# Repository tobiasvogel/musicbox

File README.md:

# MIDI Music Box

This is an improved version of the original musicbox project by [mitxela](https://github.com/mitxela/musicbox).

There are two major enhancements over the original version:
 - PCBs (Gerber and EAGLE) for the circuits as well as most of the mechanical parts
 - A (optional) addon-board featuring a Arduino MKR WiFi 1010 providing MIDI-file support from both microSD-cards and via WiFi (Webbrowser)

In the future I will furthermore add:
 * *BOM for all PCBs* (work-in-progress)
 * Renderings for visualization
 * Detailed assembly instructions

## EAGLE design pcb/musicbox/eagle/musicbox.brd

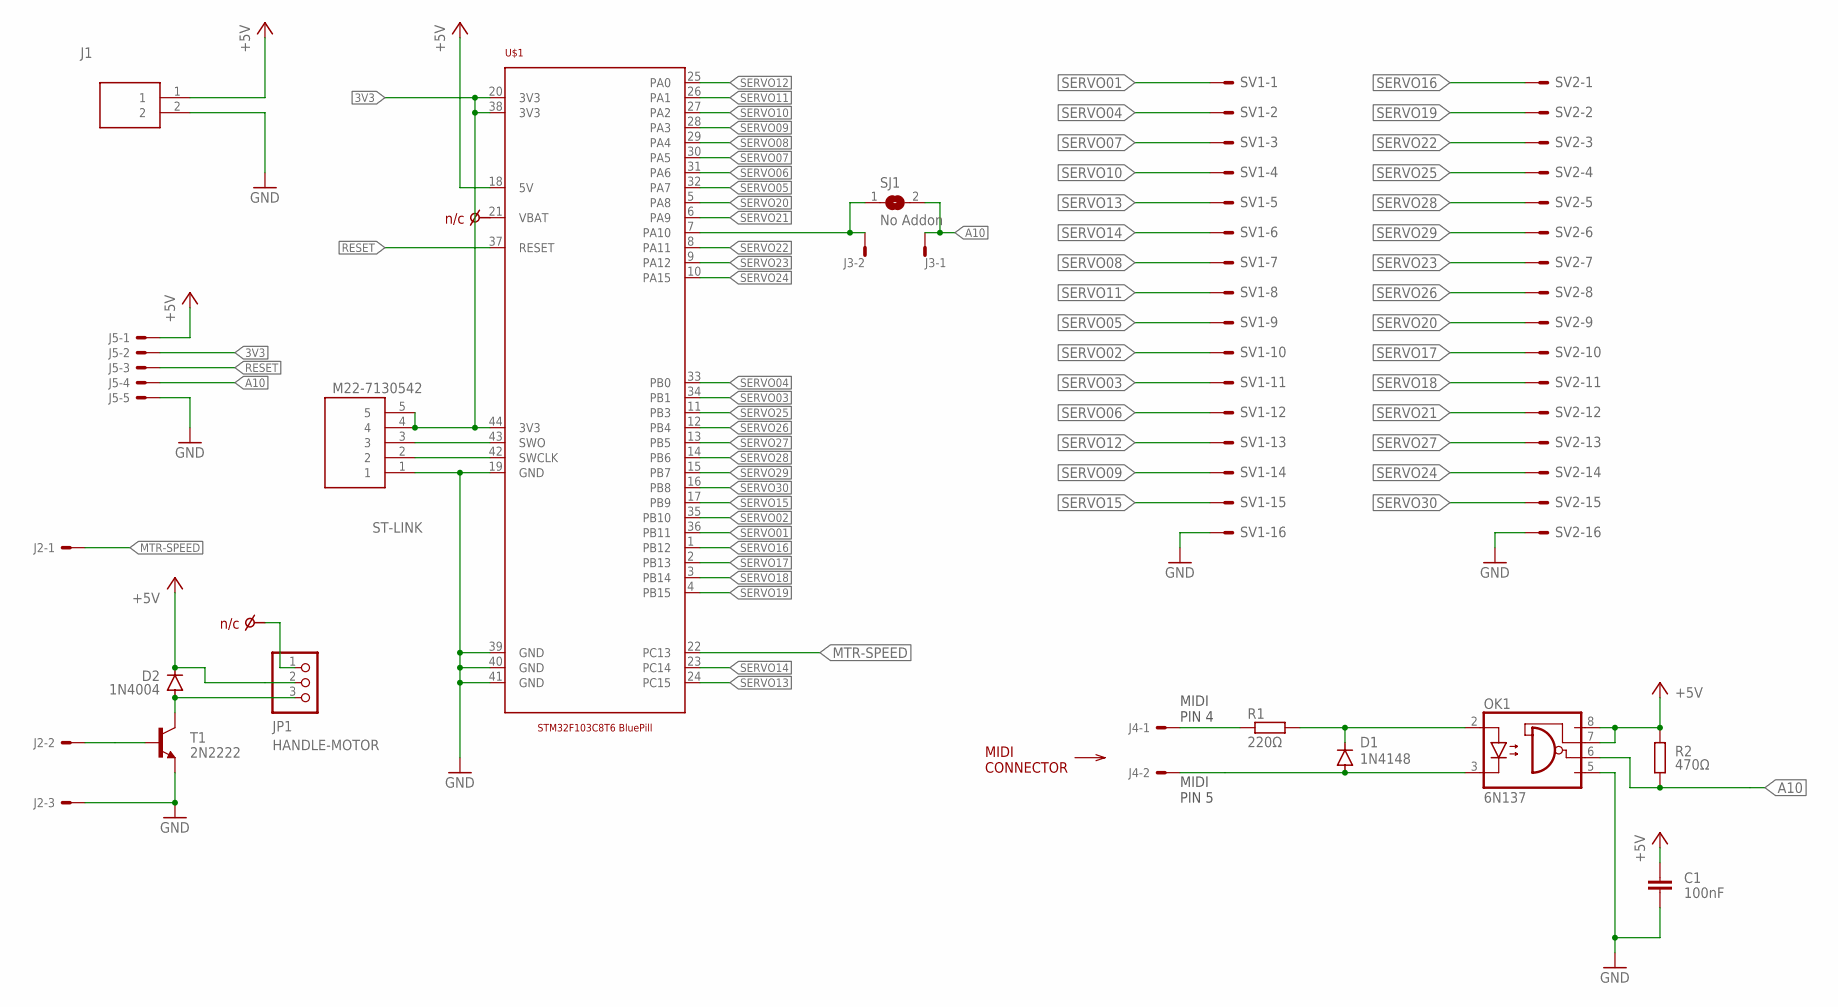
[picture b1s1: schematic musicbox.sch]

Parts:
C1: 100nF; C025-025X050; MOUSER_PART_NUMBER 594-K104M15X7RF53L2; DIGIKEY_PART_NUMBER BC5142-ND
D1: 1N4148; DO35-7; MOUSER_PART_NUMBER 512-1N4148; DIGIKEY_PART_NUMBER 1N4148FS-ND
D2: 1N4004; DO41-10; MOUSER_PART_NUMBER 583-1N4004-T; DIGIKEY_PART_NUMBER 1N4004MSCT-ND
J1: 1727010; DIGIKEY_PART_NUMBER 277-1947-ND
J2: 22-27-2031-03; 6410-03; MOUSER_PART_NUMBER 538-22-27-2031; DIGIKEY_PART_NUMBER WM4112-ND
J3, J4: 22-27-2021-02; 6410-02; MOUSER_PART_NUMBER 538-22-27-2021; DIGIKEY_PART_NUMBER WM4111-ND
J5: 22-27-2051-05; 6410-05; MOUSER_PART_NUMBER 538-22-27-2051; DIGIKEY_PART_NUMBER WM4114-ND
JP1: HANDLE-MOTOR; 1X03; MOUSER_PART_NUMBER 651-1012937890301BLF; DIGIKEY_PART_NUMBER 68004-403-ND
OK1: 6N137; DIL08; MOUSER_PART_NUMBER 859-6N137; DIGIKEY_PART_NUMBER 160-1791-ND
R1: 220Ω; 0207/7; MOUSER_PART_NUMBER 594-MBB02070C2200FCT; DIGIKEY_PART_NUMBER BC3666CT-ND
R2: 470Ω; 0207/7; MOUSER_PART_NUMBER 594-MBB02070C4700FCT; DIGIKEY_PART_NUMBER BC3790CT-ND
SJ1: No Addon; SJW
ST-LINK: M22-7130542; RHDR5W50P0X200_1X5_1050X240X44; DIGIKEY_PART_NUMBER 952-1352-5-ND
SV1: Servos 01-15; ML16; MOUSER_PART_NUMBER 617-09185166324; DIGIKEY_PART_NUMBER 1195-1694-ND
SV2: Servos 16-30; ML16; MOUSER_PART_NUMBER 617-09185166324; DIGIKEY_PART_NUMBER 1195-1694-ND
T1: 2N2222; TO92; MOUSER_PART_NUMBER 637-2N2222A; DIGIKEY_PART_NUMBER KSP2222ABUFS-ND
U$1: STM32F103C8T6BLUEPILL; STM32F103C8T6

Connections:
3V3: J5.2, ST-LINK.4, ST-LINK.5, U$1.20 (3V3), U$1.38 (3V3), U$1.44 (3V3)
+5V: C1.1, D2.C, J1.1, J5.1, JP1.2, OK1.7 (VE), OK1.8 (VCC), R2.2, U$1.18 (5V)
A10: J3.1, J5.4, OK1.6 (VO), R2.1, SJ1.2
CLK: ST-LINK.2, U$1.42 (SWCLK)
DIO: ST-LINK.3, U$1.43 (SWO)
GND: C1.2, J1.2, J2.3, J5.5, OK1.5 (GND), ST-LINK.1, SV1.16, SV2.16, T1.3 (E), U$1.19 (GND), U$1.39 (GND), U$1.40 (GND), U$1.41 (GND)
MTR-SPEED: J2.1, U$1.22 (PC13)
unnamed: J2.2, T1.2 (B)
unnamed: J4.1, R1.1
unnamed: D2.A, JP1.3, T1.1 (C)
unnamed: D1.A, J4.2, OK1.3 (C)
unnamed: D1.C, OK1.2 (A), R1.2
unnamed: J3.2, SJ1.1, U$1.7 (PA10)
RESET: J5.3, U$1.37 (RESET)
SERVO01: SV1.1, U$1.36 (PB11)
SERVO02: SV1.10, U$1.35 (PB10)
SERVO03: SV1.11, U$1.34 (PB1)
SERVO04: SV1.2, U$1.33 (PB0)
SERVO05: SV1.9, U$1.32 (PA7)
SERVO06: SV1.12, U$1.31 (PA6)
SERVO07: SV1.3, U$1.30 (PA5)
SERVO08: SV1.7, U$1.29 (PA4)
SERVO09: SV1.14, U$1.28 (PA3)
SERVO10: SV1.4, U$1.27 (PA2)
SERVO11: SV1.8, U$1.26 (PA1)
SERVO12: SV1.13, U$1.25 (PA0)
SERVO13: SV1.5, U$1.24 (PC15)
SERVO14: SV1.6, U$1.23 (PC14)
SERVO15: SV1.15, U$1.17 (PB9)
SERVO16: SV2.1, U$1.1 (PB12)
SERVO17: SV2.10, U$1.2 (PB13)
SERVO18: SV2.11, U$1.3 (PB14)
SERVO19: SV2.2, U$1.4 (PB15)
SERVO20: SV2.9, U$1.5 (PA8)
SERVO21: SV2.12, U$1.6 (PA9)
SERVO22: SV2.3, U$1.8 (PA11)
SERVO23: SV2.7, U$1.9 (PA12)
SERVO24: SV2.14, U$1.10 (PA15)
SERVO25: SV2.4, U$1.11 (PB3)
SERVO26: SV2.8, U$1.12 (PB4)
SERVO27: SV2.13, U$1.13 (PB5)
SERVO28: SV2.5, U$1.14 (PB6)
SERVO29: SV2.6, U$1.15 (PB7)
SERVO30: SV2.15, U$1.16 (PB8)

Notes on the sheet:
MIDI PIN 5
MIDI PIN 4
MIDI CONNECTOR

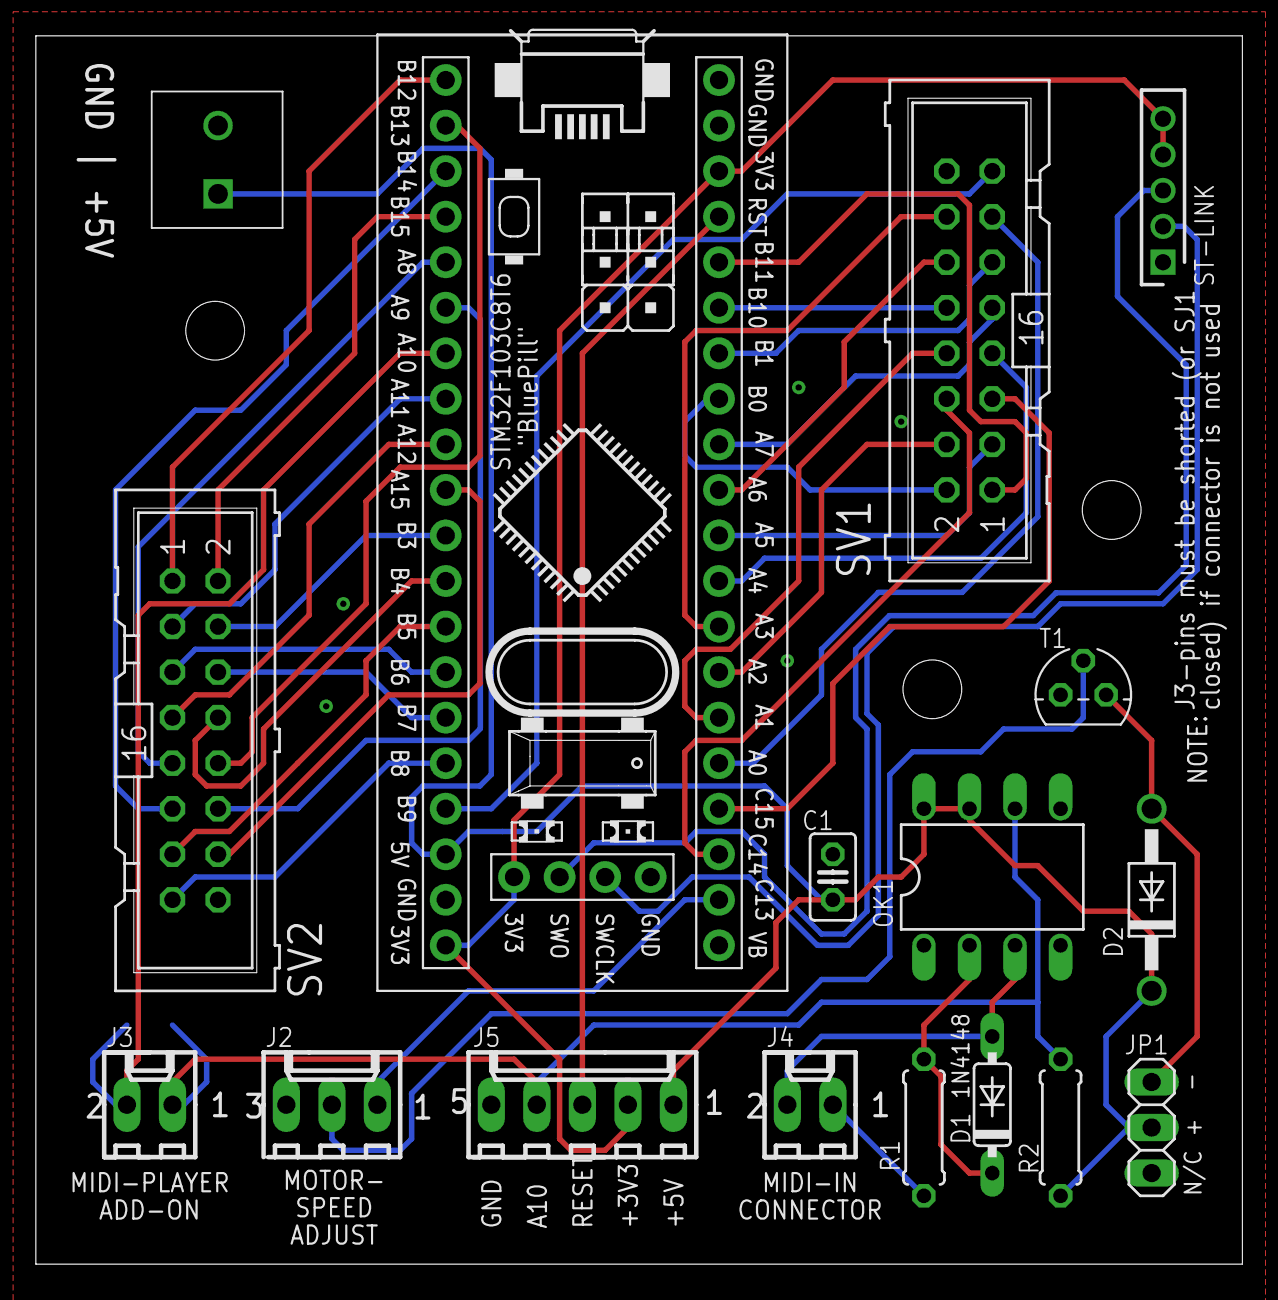
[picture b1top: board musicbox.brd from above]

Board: 2 copper layers, 67.3 x 68.5 mm, 18 parts (1 on the bottom side), 44 nets.

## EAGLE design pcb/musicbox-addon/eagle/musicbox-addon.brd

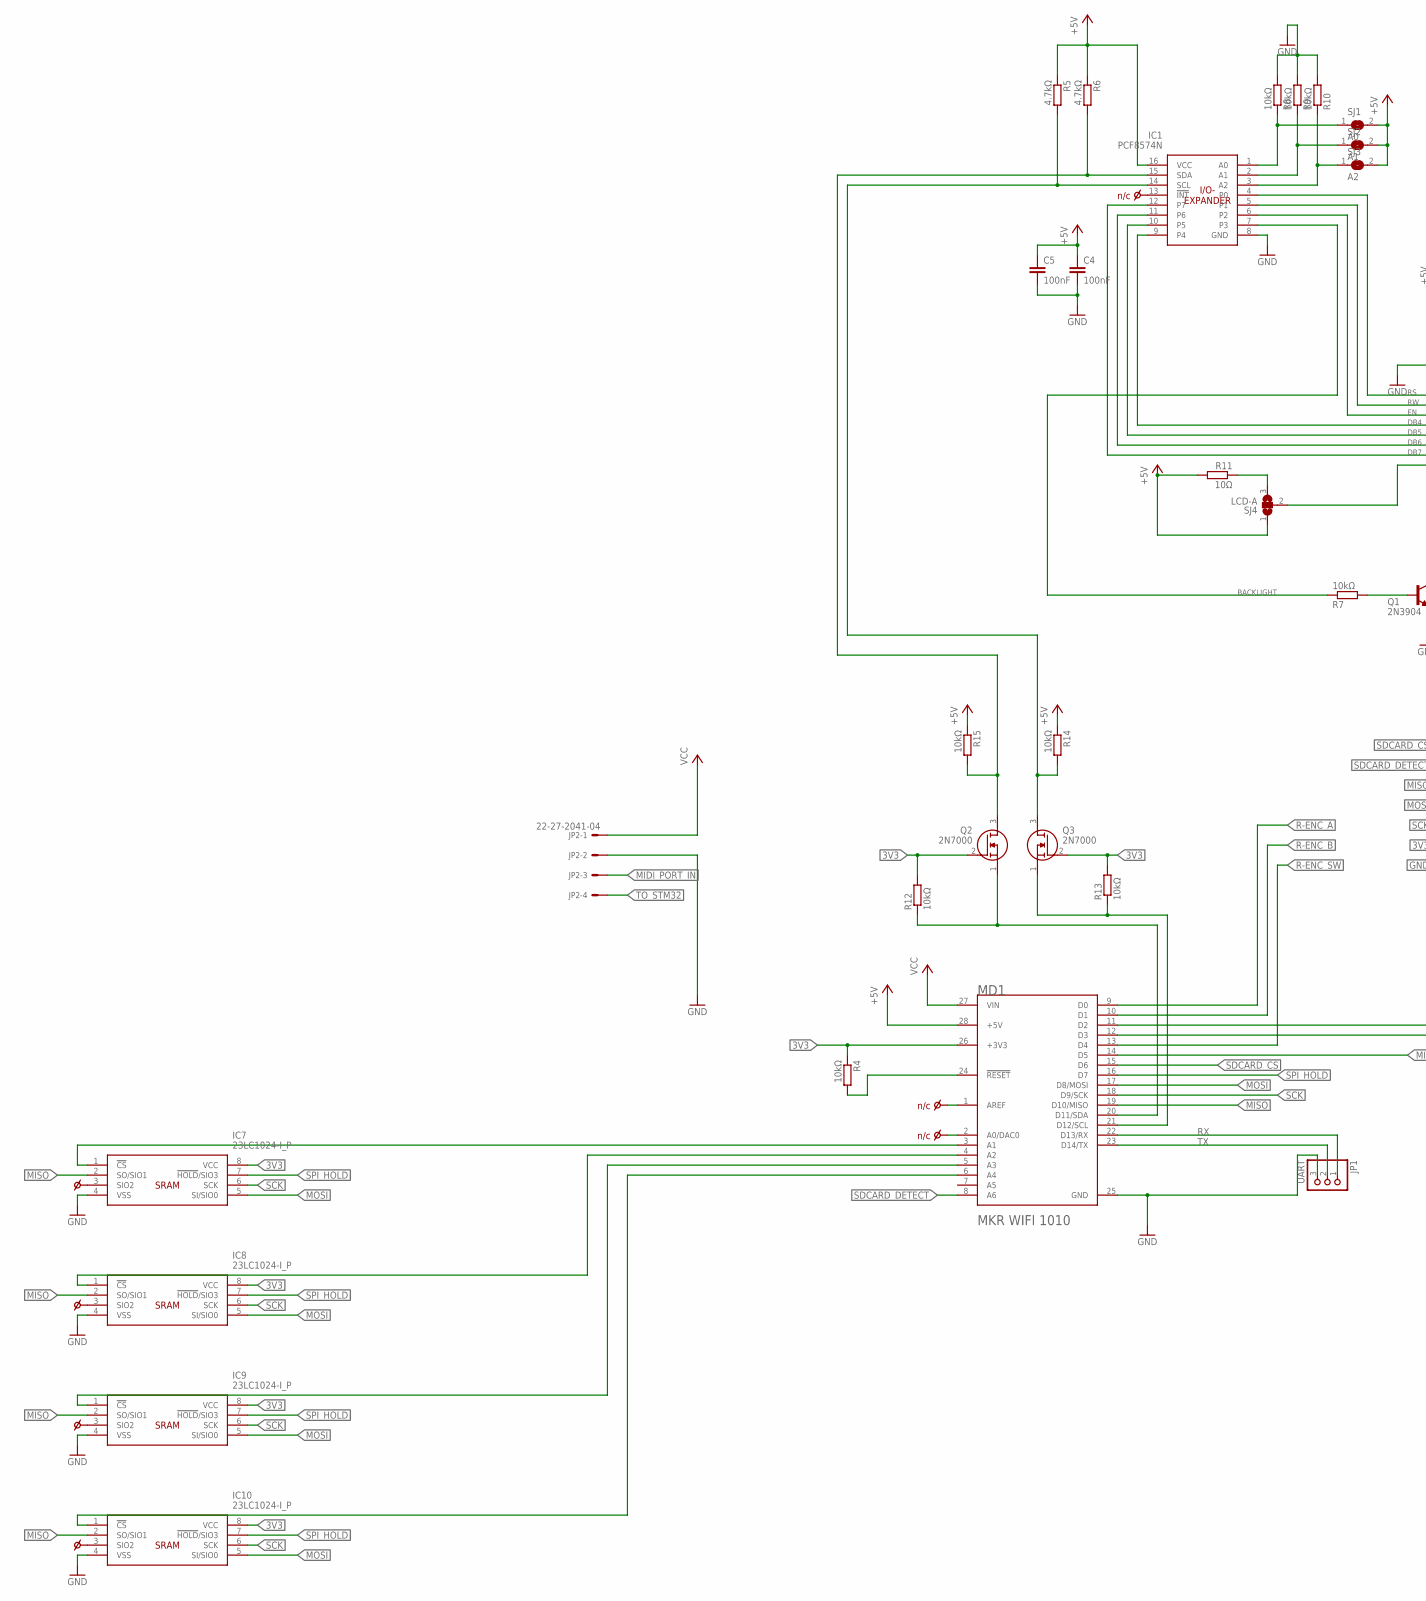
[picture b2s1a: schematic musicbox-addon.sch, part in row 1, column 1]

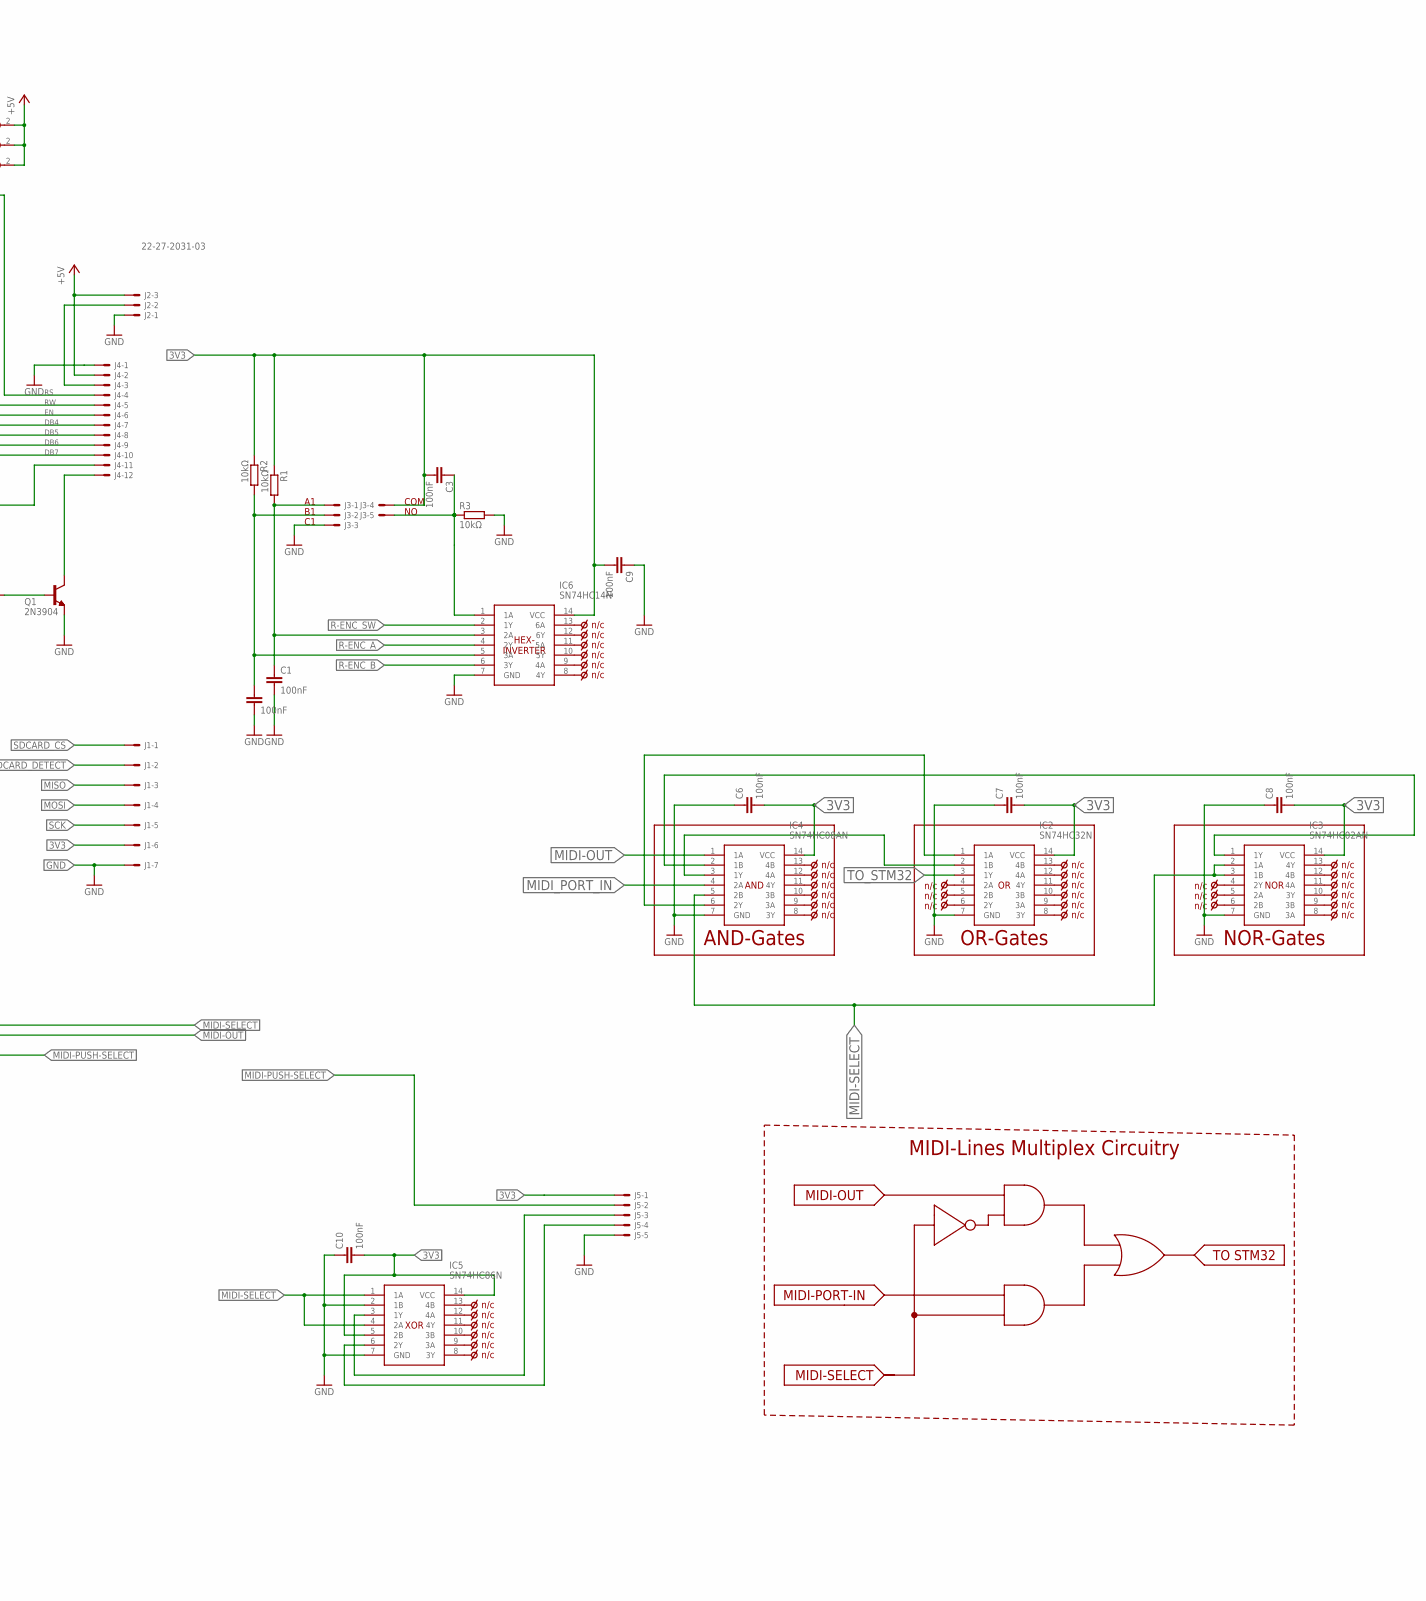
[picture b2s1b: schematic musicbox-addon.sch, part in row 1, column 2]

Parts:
C1, C2, C3, C4, C5, C6, C7, C8, C9, C10: 100nF; C025-025X050; MOUSER_PART_NUMBER 594-K104M15X7RF53L2; DIGIKEY_PART_NUMBER BC5142-ND
IC1: PCF8574N; DIP794W53P254L1930H508Q16N; DIGIKEY_PART_NUMBER 296-13109-5-ND
IC2: SN74HC32N; DIP794W53P254L1930H508Q14N; DIGIKEY_PART_NUMBER 296-1589-5-ND
IC3: SN74HC02AN; DIP794W53P254L1930H508Q14N; DIGIKEY_PART_NUMBER 296-SN74HC02AN-ND
IC4: SN74HC08AN; DIP794W53P254L1930H508Q14N; DIGIKEY_PART_NUMBER 296-1570-5-ND
IC5: SN74HC86N; DIP794W53P254L1930H508Q14N; DIGIKEY_PART_NUMBER 296-8375-5-ND
IC6: SN74HC14N; DIP794W53P254L1930H508Q14N; DIGIKEY_PART_NUMBER 296-1577-5-ND
IC7, IC8, IC9, IC10: 23LC1024-I_P; DIP781W56P254L950H533Q8N; DIGIKEY_PART_NUMBER 23LC1024-I/P-ND
J1: 22-27-2071-07; 6410-07; MOUSER_PART_NUMBER 538-22-27-2071; DIGIKEY_PART_NUMBER WM4116-ND
J2: 22-27-2031-03; 6410-03; MOUSER_PART_NUMBER 538-22-27-2031; DIGIKEY_PART_NUMBER WM4112-ND
J3, J5: 22-27-2051-05; 6410-05; MOUSER_PART_NUMBER 538-22-27-2051; DIGIKEY_PART_NUMBER WM4114-ND
J4: 22-27-2121-12; 6410-12; MOUSER_PART_NUMBER 538-22-27-2121; DIGIKEY_PART_NUMBER 23-0022272121-ND
JP1: UART; 1X03; MOUSER_PART_NUMBER 649-1012937890301BLF; DIGIKEY_PART_NUMBER 68002-403-ND
JP2: 22-27-2041-04; 6410-04
MD1: ARDUINO_MKR_WIFI_1010ARDUINO_MKR_WIFI_1010_0_0; ARDUINO_MKR_WIFI_1010_0; FARNELL_PART_NUMBER 2917569
Q1: 2N3904; TO92; MOUSER_PART_NUMBER 610-2N3904; DIGIKEY_PART_NUMBER 1514-2N3904PBFREE-ND
Q2, Q3: 2N7000; TO-92_(TO-226); DIGIKEY_PART_NUMBER 2N7000FS-ND
R1, R2, R3, R4, R7, R8, R9, R10, R12, R13, R14, R15: 10kΩ; 0207/7; MOUSER_PART_NUMBER 594-MBB02070C1002FCT; DIGIKEY_PART_NUMBER BC3569CT-ND
R5, R6: 4.7kΩ; 0207/7; MOUSER_PART_NUMBER 594-MBB02070C4701FCT; DIGIKEY_PART_NUMBER BC3792CT-ND
R11: 10Ω; 0207/7; MOUSER_PART_NUMBER 594-MBB02070C3300FCT; DIGIKEY_PART_NUMBER BC3741CT-ND
SJ1: A0; SJ
SJ2: A1; SJ
SJ3: A2; SJ
SJ4: LCD-A; SJ_2

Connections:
3V3: C3.2, C6.2, C7.2, C8.2, C9.2, C10.2, IC2.14 (VCC), IC3.14 (VCC), IC4.14 (VCC), IC5.5 (2B), IC5.14 (VCC), IC6.14 (VCC), IC7.8 (VCC), IC8.8 (VCC), IC9.8 (VCC), IC10.8 (VCC), J1.6, J3.4, J5.1, MD1.26 (+3V3), Q2.2 (G), Q3.2 (G), R1.1, R2.1, R4.1, R12.2, R13.2
+5V: C4.1, C5.1, IC1.16 (VCC), J2.3, J4.2, MD1.28 (+5V), R5.1, R6.1, R11.2, R14.1, R15.1, SJ1.2, SJ2.2, SJ3.2, SJ4.1
BACKLIGHT: IC1.7 (P3), R7.1
DB4: IC1.9 (P4), J4.7
DB5: IC1.10 (P5), J4.8
DB6: IC1.11 (P6), J4.9
DB7: IC1.12 (P7), J4.10
EN: IC1.6 (P2), J4.6
GND: C1.2, C2.2, C4.2, C5.2, C6.1, C7.1, C8.1, C9.1, C10.1, IC1.8 (GND), IC2.7 (GND), IC3.7 (GND), IC4.7 (GND), IC5.2 (1B), IC5.7 (GND), IC6.7 (GND), IC7.4 (VSS), IC8.4 (VSS), IC9.4 (VSS), IC10.4 (VSS), J1.7, J2.1, J3.3, J4.1, J5.5, JP1.3, JP2.2, MD1.25 (GND), Q1.3 (E), R3.2, R8.2, R9.2, R10.2
I2C_SCL: IC1.14 (SCL), Q3.3 (D), R5.2, R14.2
I2C_SDA: IC1.15 (SDA), Q2.3 (D), R6.2, R15.2
MIDI-OUT: IC4.1 (1A), MD1.12 (D3)
MIDI-PUSH-SELECT: J5.2, MD1.14 (D5)
MIDI-SELECT: IC3.2 (1A), IC3.3 (1B), IC4.5 (2B), IC5.1 (1A), IC5.4 (2A), MD1.11 (D2)
MIDI_PORT_IN: IC4.4 (2A), JP2.3
MISO: IC7.2 (SO/SIO1), IC8.2 (SO/SIO1), IC9.2 (SO/SIO1), IC10.2 (SO/SIO1), J1.3, MD1.19 (D10/MISO)
MOSI: IC7.5 (SI/SIO0), IC8.5 (SI/SIO0), IC9.5 (SI/SIO0), IC10.5 (SI/SIO0), J1.4, MD1.17 (D8/MOSI)
unnamed: IC1.3 (A2), R10.1, SJ3.1
unnamed: IC1.1 (A0), R8.1, SJ1.1
unnamed: IC1.2 (A1), R9.1, SJ2.1
unnamed: C3.1, IC6.1 (1A), J3.5, R3.1
unnamed: MD1.24 (!RESET!), R4.2
unnamed: MD1.21 (D12/SCL), Q3.1 (S), R13.1
unnamed: IC2.2 (1B), IC4.3 (1Y)
unnamed: IC3.1 (1Y), IC4.2 (1B)
unnamed: IC2.1 (1A), IC4.6 (2Y)
unnamed: J4.11, SJ4.2
unnamed: R11.1, SJ4.3
unnamed: IC5.3 (1Y), J5.3
unnamed: IC5.6 (2Y), J5.4
unnamed: MD1.20 (D11/SDA), Q2.1 (S), R12.1
unnamed: Q1.2 (B), R7.2
unnamed: J2.2, J4.3
unnamed: IC7.1 (!CS), MD1.3 (A1)
unnamed: IC8.1 (!CS), MD1.4 (A2)
unnamed: IC9.1 (!CS), MD1.5 (A3)
unnamed: IC10.1 (!CS), MD1.6 (A4)
unnamed: J4.12, Q1.1 (C)
R-ENC_A: IC6.4 (2Y), MD1.9 (D0)
R-ENC_B: IC6.6 (3Y), MD1.10 (D1)
R-ENC_SW: IC6.2 (1Y), MD1.13 (D4)
RS: IC1.4 (P0), J4.4
RW: IC1.5 (P1), J4.5
RX: JP1.1, MD1.22 (D13/RX)
R_ENC_A: C1.1, IC6.3 (2A), J3.1, R1.2
R_ENC_B: C2.1, IC6.5 (3A), J3.2, R2.2
SCK: IC7.6 (SCK), IC8.6 (SCK), IC9.6 (SCK), IC10.6 (SCK), J1.5, MD1.18 (D9/SCK)
SDCARD_CS: J1.1, MD1.15 (D6)
SDCARD_DETECT: J1.2, MD1.8 (A6)
SPI_HOLD: IC7.7 (!HOLD!/SIO3), IC8.7 (!HOLD!/SIO3), IC9.7 (!HOLD!/SIO3), IC10.7 (!HOLD!/SIO3), MD1.16 (D7)
TO_STM32: IC2.3 (1Y), JP2.4
TX: JP1.2, MD1.23 (D14/TX)
VCC: JP2.1, MD1.27 (VIN)

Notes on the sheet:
AND-Gates
OR-Gates
NOR-Gates
MIDI-Lines Multiplex Circuitry
MIDI-OUT
MIDI-PORT-IN
TO STM32
MIDI-SELECT
COM
XOR
AND
NOR
HEX- INVERTER
I/O- EXPANDER
SRAM

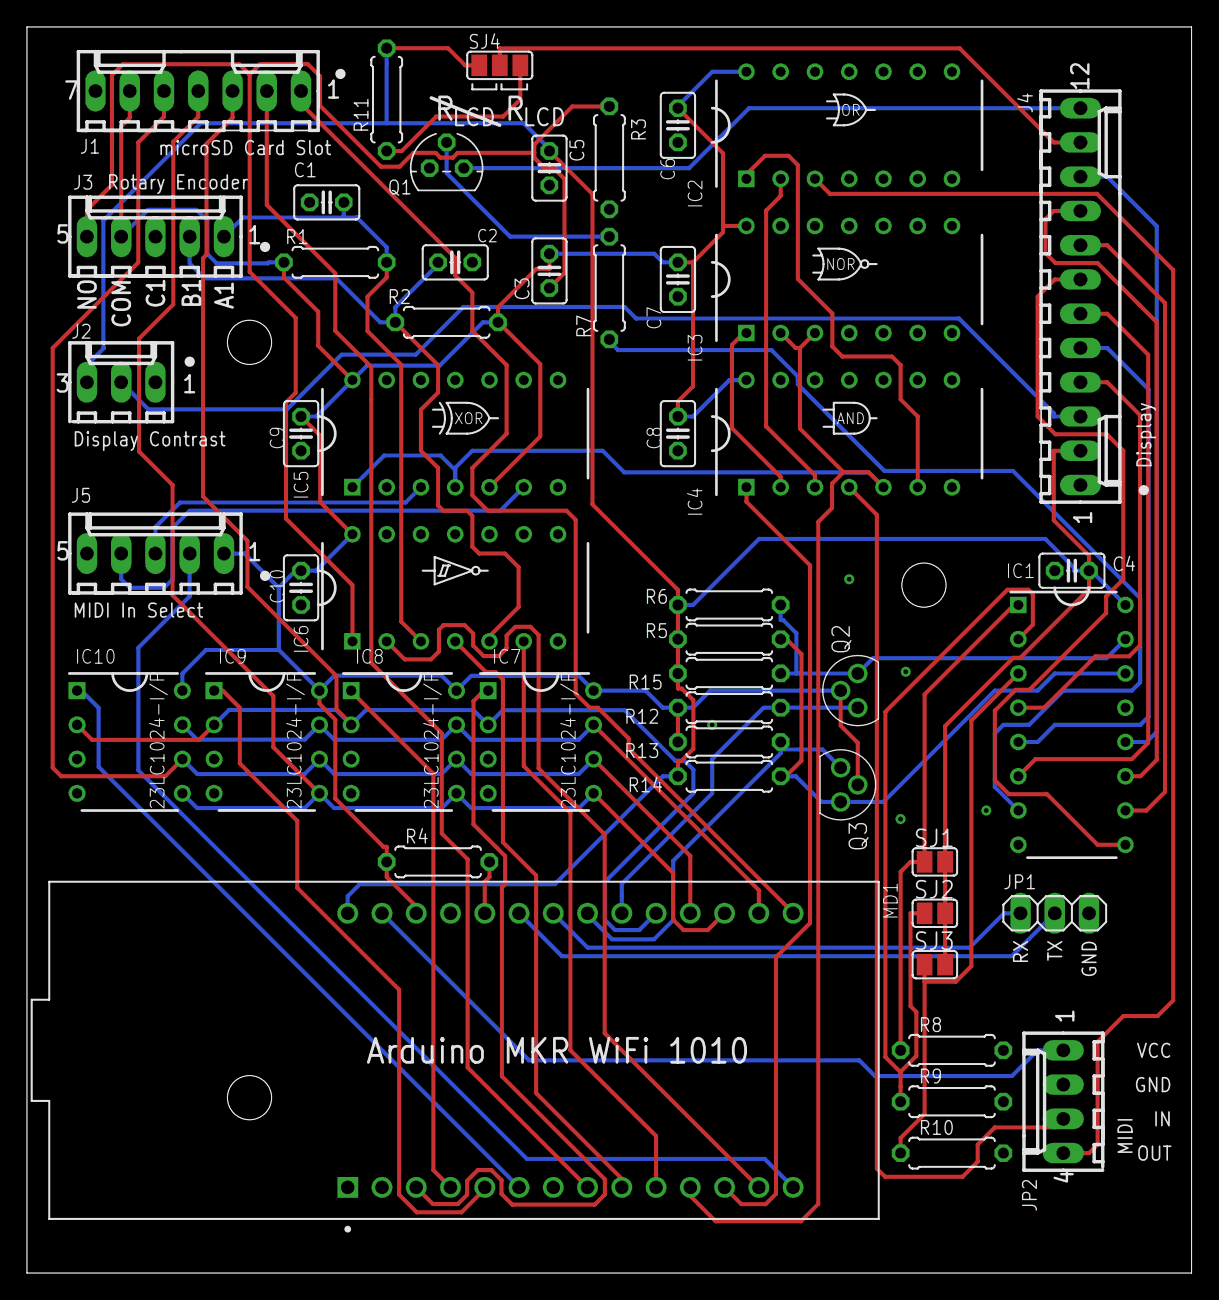
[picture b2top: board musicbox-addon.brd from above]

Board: 2 copper layers, 86.3 x 92.4 mm, 50 parts (0 on the bottom side), 53 nets.

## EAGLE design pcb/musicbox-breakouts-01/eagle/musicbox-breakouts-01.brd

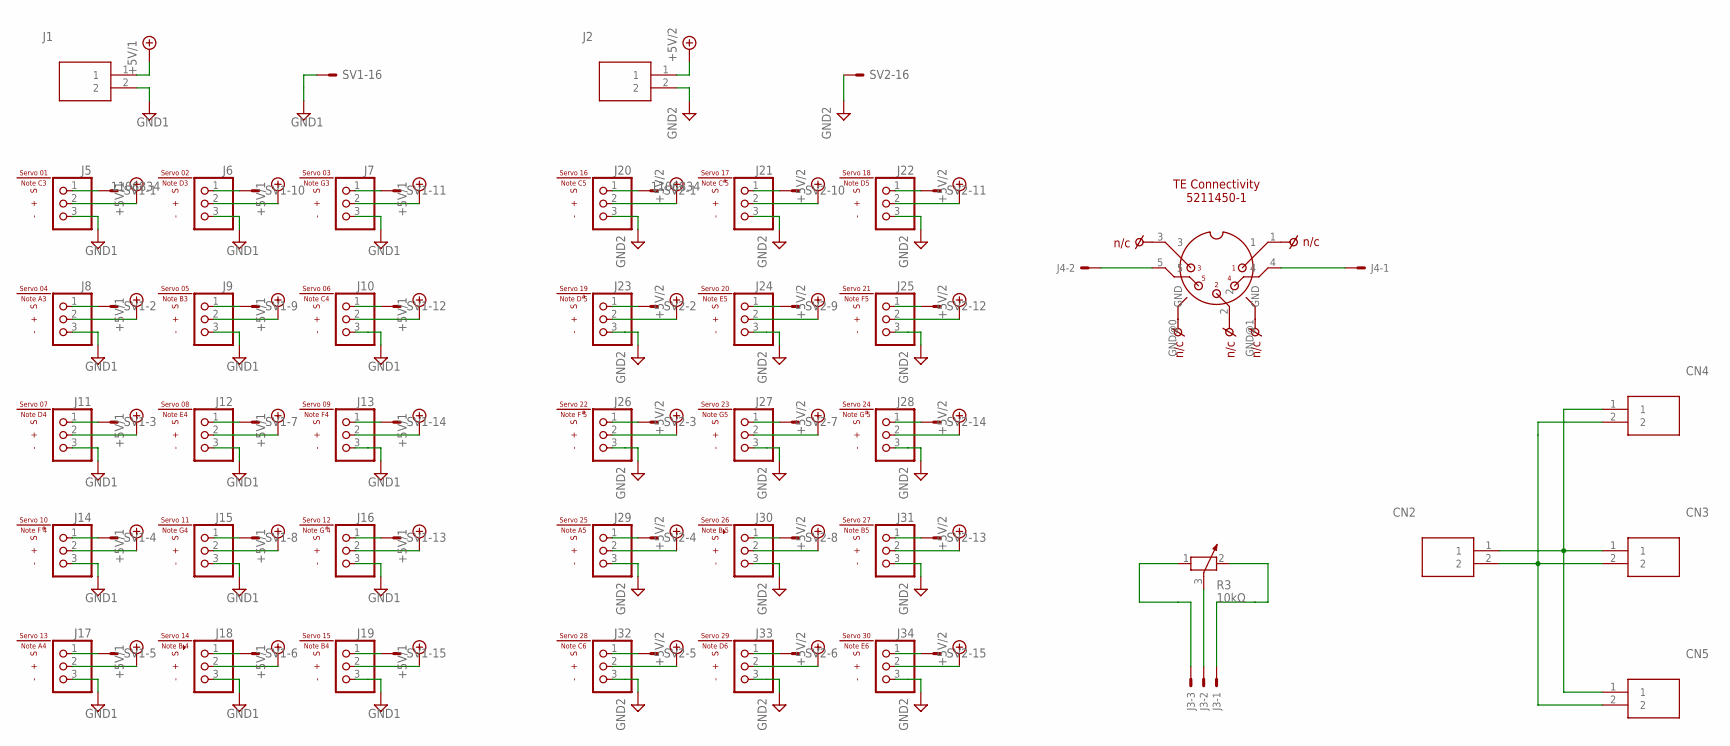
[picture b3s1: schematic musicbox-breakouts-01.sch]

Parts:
CN1: 5211450-1; MOUSER_PART_NUMBER 571-5211450-1; DIGIKEY_PART_NUMBER 5211450-1-ND
CN2, CN3, CN4, CN5: 1727010; DIGIKEY_PART_NUMBER 277-1947-ND
J1, J2: 1727010; DIGIKEY_PART_NUMBER 277-1947-ND
J3: 22-05-7038-03; 7395-03; MOUSER_PART_NUMBER 538-22-05-7038; DIGIKEY_PART_NUMBER WM2785-ND
J4: 22-27-2021-02; 6410-02; MOUSER_PART_NUMBER 538-22-27-2021; DIGIKEY_PART_NUMBER WM4111-ND
J5, J6, J7, J8, J9, J10, J11, J12, J13, J14, J15, J16, J17, J18, J19, J20, J21, J22, J23, J24, J25, J26, J27, J28, J29, J30, J31, J32, J33, J34: PINHD-1X3; 1X03; MOUSER_PART_NUMBER 649-1012937890301BLF; DIGIKEY_PART_NUMBER 68004-403-ND
R3: 10kΩ; PT-10; MOUSER_PART_NUMBER 531-PT10MV1103A11PMS; DIGIKEY_PART_NUMBER 1993-PT10MV10-103A1010-PM-S-ND
SV1, SV2: ML16E; ML16; MOUSER_PART_NUMBER 617-09185166324; DIGIKEY_PART_NUMBER 1195-1694-ND
U$1, U$2, U$3, U$4, U$5, U$6, U$7, U$8, U$9, U$10, U$11, U$12, U$13, U$14, U$15, U$16, U$17, U$18, U$19, U$20, U$21, U$22, U$23, U$24, U$25, U$26, U$27, U$28, U$29, U$30: SERVO-SMALL
U$41: SERVO01_NOTEC3; SERVO_1/NOTE_C3
U$42: SERVO02_NOTED3; SERVO_2/NOTE_D3
U$43: SERVO03_NOTEG3; SERVO_3/NOTE_G3
U$44: SERVO04_NOTEA3; SERVO_4/NOTE_A3
U$45: SERVO05_NOTEB3; SERVO_5/NOTE_B3
U$46: SERVO06_NOTEC4; SERVO_6/NOTE_C4
U$47: SERVO07_NOTED4; SERVO_7/NOTE_D4
U$48: SERVO08_NOTEE4; SERVO_8/NOTE_E4
U$49: SERVO09_NOTEF4; SERVO_9/NOTE_F4
U$50: SERVO10_NOTEF#4; SERVO_10/NOTE_F#4
U$51: SERVO11_NOTEG4; SERVO_11/NOTE_G4
U$52: SERVO12_NOTEG#4; SERVO_12/NOTE_G#4
U$53: SERVO13_NOTEA4; SERVO_13/NOTE_A4
U$54: SERVO14_NOTEBB4; SERVO_14/NOTE_BB4
U$55: SERVO15_NOTEB4; SERVO_15/NOTE_B4
U$56: SERVO16_NOTEC5; SERVO_16/NOTE_C5
U$57: SERVO17_NOTEC#5; SERVO_17/NOTE_C#5
U$58: SERVO18_NOTED5; SERVO_18/NOTE_D5
U$59: SERVO19_NOTED#5; SERVO_19/NOTE_D#5
U$60: SERVO20_NOTEE5; SERVO_20/NOTE_E5
U$61: SERVO21_NOTEF5; SERVO_21/NOTE_F5
U$62: SERVO22_NOTEF#5; SERVO_22/NOTE_F#5
U$63: SERVO23_NOTEG5; SERVO_23/NOTE_G5
U$64: SERVO24_NOTEG#5; SERVO_24/NOTE_G#5
U$65: SERVO25_NOTEA5; SERVO_25/NOTE_A5
U$66: SERVO26_NOTEBB5; SERVO_26/NOTE_BB5
U$67: SERVO27_NOTEB5; SERVO_27/NOTE_B5
U$69: SERVO28_NOTEC6; SERVO_28/NOTE_C6
U$70: SERVO29_NOTED6; SERVO_29/NOTE_D6
U$71: SERVO30_NOTEE6; SERVO_30/NOTE_E6

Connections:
+5V: J1.1, J5.2, J6.2, J7.2, J8.2, J9.2, J10.2, J11.2, J12.2, J13.2, J14.2, J15.2, J16.2, J17.2, J18.2, J19.2
GND: J1.2, J5.3, J6.3, J7.3, J8.3, J9.3, J10.3, J11.3, J12.3, J13.3, J14.3, J15.3, J16.3, J17.3, J18.3, J19.3, SV1.16
unnamed: J5.1, SV1.1
unnamed: J8.1, SV1.2
unnamed: J11.1, SV1.3
unnamed: J14.1, SV1.4
unnamed: J17.1, SV1.5
unnamed: J16.1, SV1.13
unnamed: J19.1, SV1.15
unnamed: J13.1, SV1.14
unnamed: J10.1, SV1.12
unnamed: J7.1, SV1.11
unnamed: J6.1, SV1.10
unnamed: J9.1, SV1.9
unnamed: J12.1, SV1.7
unnamed: J15.1, SV1.8
unnamed: J18.1, SV1.6
unnamed: J20.1, SV2.1
unnamed: J21.1, SV2.10
unnamed: J22.1, SV2.11
unnamed: J24.1, SV2.9
unnamed: J23.1, SV2.2
unnamed: J25.1, SV2.12
unnamed: J26.1, SV2.3
unnamed: J27.1, SV2.7
unnamed: J28.1, SV2.14
unnamed: J29.1, SV2.4
unnamed: J30.1, SV2.8
unnamed: J31.1, SV2.13
unnamed: J32.1, SV2.5
unnamed: J33.1, SV2.6
unnamed: J34.1, SV2.15
unnamed: CN2.1, CN3.1, CN4.1, CN5.1
unnamed: CN2.2, CN3.2, CN4.2, CN5.2
unnamed: J3.3, R3.1
unnamed: J3.2, R3.3
unnamed: J3.1, R3.2
unnamed: CN1.4, J4.1
unnamed: CN1.5, J4.2
VCC: J2.1, J20.2, J21.2, J22.2, J23.2, J24.2, J25.2, J26.2, J27.2, J28.2, J29.2, J30.2, J31.2, J32.2, J33.2, J34.2
VSS: J2.2, J20.3, J21.3, J22.3, J23.3, J24.3, J25.3, J26.3, J27.3, J28.3, J29.3, J30.3, J31.3, J32.3, J33.3, J34.3, SV2.16

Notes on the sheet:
TE Connectivity 5211450-1

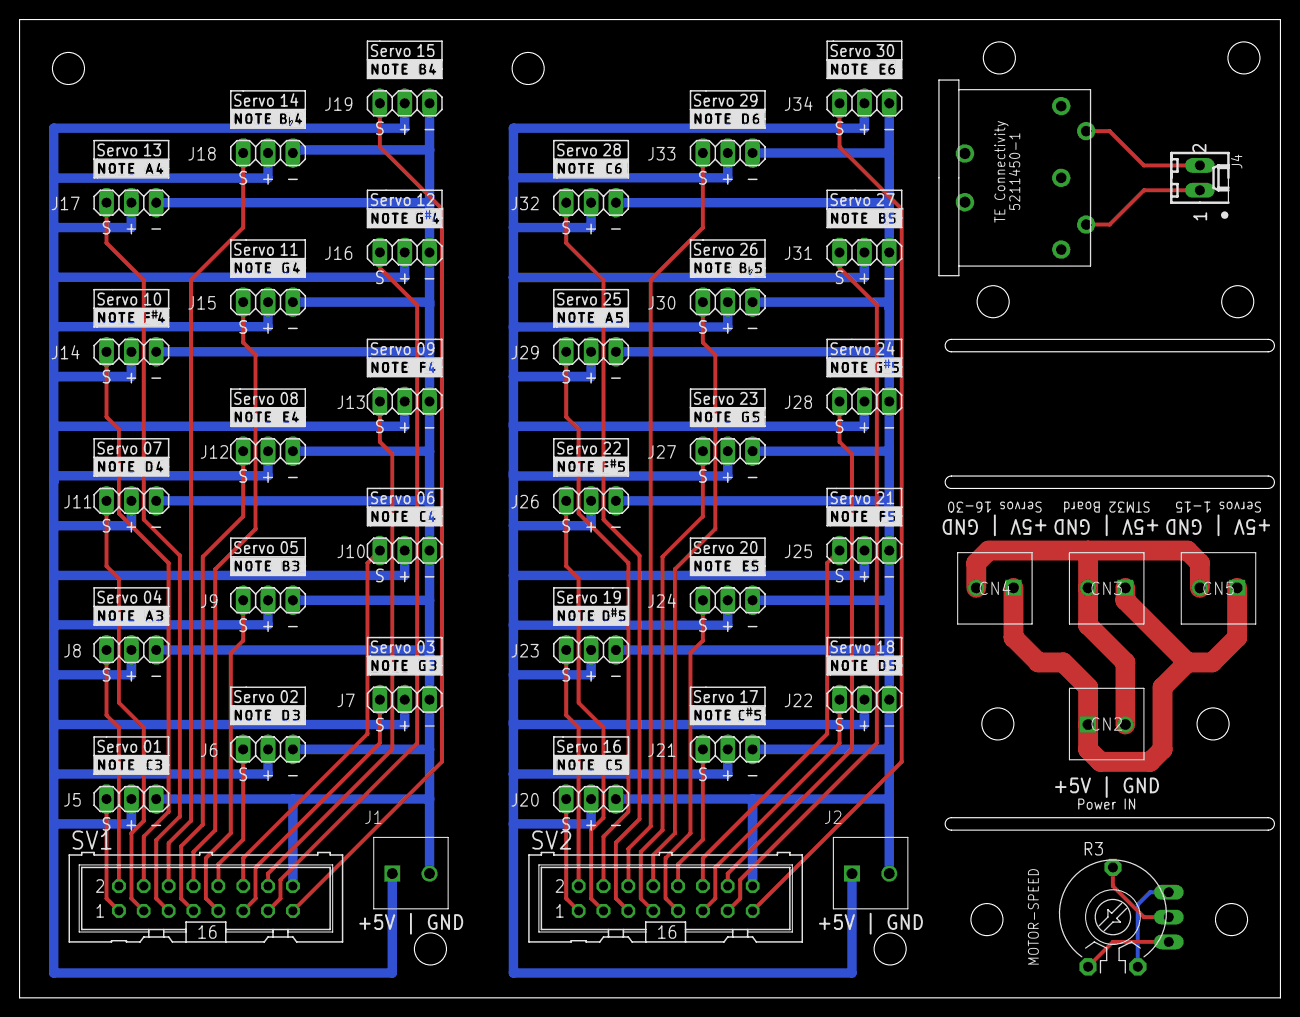
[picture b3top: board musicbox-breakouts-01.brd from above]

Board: 2 copper layers, 128.9 x 100.0 mm, 102 parts (1 on the bottom side), 41 nets.

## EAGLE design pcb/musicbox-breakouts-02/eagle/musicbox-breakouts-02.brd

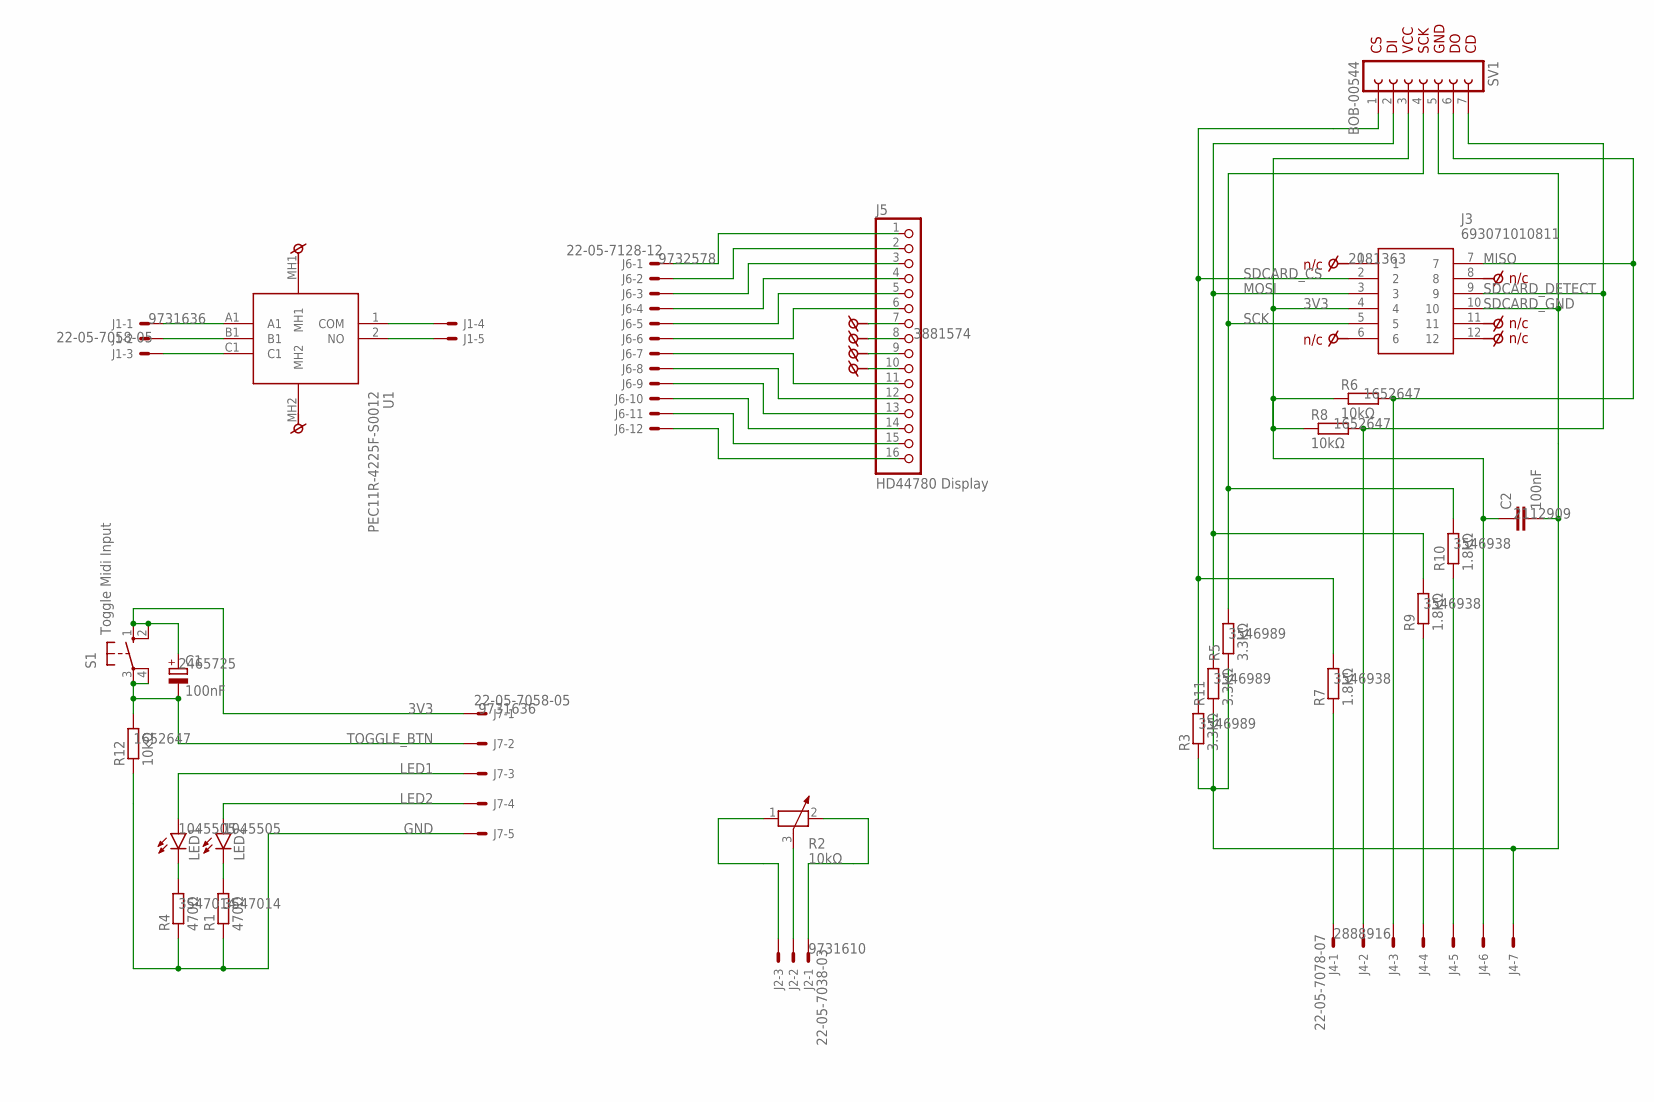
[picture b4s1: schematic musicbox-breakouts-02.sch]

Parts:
C1: 100nF; E1,8-4; MOUSER_PART_NUMBER 710-860010672001; DIGIKEY_PART_NUMBER 732-8653-1-ND
C2: 100nF; C025-025X050; MOUSER_PART_NUMBER 594-K104M15X7RF53L2; DIGIKEY_PART_NUMBER BC5142-ND
J1, J7: 22-05-7058-05; 7395-05; MOUSER_PART_NUMBER 538-22-05-7058; DIGIKEY_PART_NUMBER WM2787-ND
J2: 22-05-7038-03; 7395-03; MOUSER_PART_NUMBER 538-22-05-7038; DIGIKEY_PART_NUMBER WM2785-ND
J3: 693071010811; DIGIKEY_PART_NUMBER 732-3819-1-ND
J4: 22-05-7078-07; 7395-07; MOUSER_PART_NUMBER 538-22-05-7078; DIGIKEY_PART_NUMBER WM17054-ND
J5: HD44780 Display; 1X16; MOUSER_PART_NUMBER 649-1012937891601BLF; DIGIKEY_PART_NUMBER 68002-116-ND
J6: 22-05-7128-12; 7395-12; MOUSER_PART_NUMBER 538-22-05-7128; DIGIKEY_PART_NUMBER WM4378-ND
LED1, LED2: LED3MM; MOUSER_PART_NUMBER 78-TLLG4401-AS12; DIGIKEY_PART_NUMBER TLLG4401-AS12CT-ND
R1, R4: 470Ω; 0207/7; MOUSER_PART_NUMBER 594-MBB02070C4700FCT; DIGIKEY_PART_NUMBER BC3790CT-ND
R2: 10kΩ; PT-10; MOUSER_PART_NUMBER 531-PT10MV1103A11PMS; DIGIKEY_PART_NUMBER 1993-PT10MV10-103A1010-PM-S-ND
R3, R5, R11: 3.3kΩ; 0207/7; MOUSER_PART_NUMBER 594-MBB02070C3301FCT; DIGIKEY_PART_NUMBER BC3743CT-ND
R6, R8, R12: 10kΩ; 0207/7; MOUSER_PART_NUMBER 594-MBB02070C1002FCT; DIGIKEY_PART_NUMBER BC3569CT-ND
R7, R9, R10: 1.8kΩ; 0207/7; MOUSER_PART_NUMBER 594-MBB02070C1801FCT; DIGIKEY_PART_NUMBER BC3638CT-ND
S1: Toggle Midi Input; B3F-10XX; MOUSER_PART_NUMBER 179-TS0266130BK160LC; DIGIKEY_PART_NUMBER 2223-TS02-66-130-BK-160-LCR-D-ND
SV1: BOB-00544; FE07
U1: PEC11R-4225F-S0012; PEC11R4225FS0012; DIGIKEY_PART_NUMBER PEC11R-4225F-S0012-ND

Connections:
3V3: C2.1, J3.4, J4.6, R6.1, R8.1, SV1.3
DISPLAY_1: J5.1, J6.1
MISO: J3.7, J4.3, R6.2, SV1.6
MOSI: J3.3, R9.2, R11.2, SV1.2
unnamed: J1.1, U1.A1
unnamed: J1.2, U1.B1
unnamed: J1.3, U1.C1
unnamed: J1.5, U1.2 (NO)
unnamed: J1.4, U1.1 (COM)
unnamed: J5.2, J6.2
unnamed: J5.3, J6.3
unnamed: J5.4, J6.4
unnamed: J5.5, J6.5
unnamed: J5.6, J6.6
unnamed: J5.16, J6.12
unnamed: J5.15, J6.11
unnamed: J5.14, J6.10
unnamed: J5.13, J6.9
unnamed: J5.12, J6.8
unnamed: J5.11, J6.7
unnamed: C1.-, J7.2, R12.2, S1.3, S1.4 (P1)
unnamed: J7.3, LED1.A
unnamed: J7.4, LED2.A
unnamed: C1.+, J7.1, S1.1 (S), S1.2 (S1)
unnamed: J7.5, R1.1, R4.1, R12.1
unnamed: LED1.K (C), R4.2
unnamed: LED2.K (C), R1.2
unnamed: J2.3, R2.1
unnamed: J2.2, R2.3
unnamed: J2.1, R2.2
unnamed: J4.1, R7.1
unnamed: J4.5, R10.1
unnamed: J4.4, R9.1
SCK: J3.5, R5.2, R10.2, SV1.4
SDCARD_CS: J3.2, R3.2, R7.2, SV1.1
SDCARD_DETECT: J3.9, J4.2, R8.2, SV1.7
SDCARD_GND: C2.2, J3.10, J4.7, R3.1, R5.1, R11.1, SV1.5

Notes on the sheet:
GND
3V3
TOGGLE_BTN
LED1
LED2
CS DI VCC SCK GND DO CD
